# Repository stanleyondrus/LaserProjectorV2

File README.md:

## Introduction
LaserProjector V2 is a battery-powered, ESP32-based laser XY scanner using stepper motors to deflect the beam. It has auto-homing functionality, and can be controlled wirelessly (Wi-Fi & Bluetooth).

## Features
- Hybrid Wi-Fi operation mode (STA & AP)
- Webserver GUI with custom WebSocket protocol
- Concurrent multi-user control
- Automatic/Manual/External scanning mode
- Parallel auto-homing
- Battery-powered

## Links
- [Documentation [stanleyprojects.com]](https://stanleyprojects.com/projects/laserprojector-v2/)
- [Article [hackaday.com]](https://hackaday.com/2022/11/02/laser-project-relies-on-steppers-rather-than-galvanometers/)
- [Video [youtube.com]](https://youtu.be/w1O48Ysdiiw)
- [Project [hackaday.io]](https://hackaday.io/project/188046-laserprojector-v2)
- [Project [hackster.io]](https://www.hackster.io/stanleyprojects/laserprojector-v2-fa77cf)

## Design

## How to build your own release
### Prerequisites
- Visual Studio Code with PlatformIO extension
- 3.3V USB to Serial (e.g. FT232RL)
### Building
1. Open __*firmware/src*__ folder in VSCode
2. In __*firmware/src/src/main.cpp*__ you can sustomize SSID and PASSWORD for Wi-Fi STA mode:
```cpp
const char* ssid = "<your_ssid>";
const char* password = "<your_pass>";
```
3. In __*firmware/src/platformio.ini*__ set the correct *_upload_port_*, or remove to auto-detect.

4. Build and upload the filesystem
    - PlatformIO > esp32serial > Platform > Build Filesystem Image
    - PlatformIO > esp32serial > Platform > Upload Filesystem Image

5. Build and upload the firmware
    - PlatformIO > esp32serial > General > Upload

## Pre-built binaries
The binary is fully contained (bootloader, firmware, and filesystem), so it can be flashed to address 0x0.

The easiest way is to use this web tool: https://stanleyprojects.com/projects/laserprojector-v2/install/index.html

After the firmware is loaded, any subsequent updates can be done OTA in browser by visiting _http://\<esp32-ip-address\>/update_

|Version|Firmware|
|-|-|
|0.1|[LaserProjectorV2_firmware_v0.1.bin](https://github.com/stanleyondrus/LaserProjectorV2/releases/download/v0.1/LaserProjectorV2_v0.1.bin)|

## Credits
- [A Beginner's Guide to the ESP8266](https://tttapa.github.io/ESP8266/Chap01%20-%20ESP8266.html)
- [ElegantOTA](https://github.com/ayushsharma82/ElegantOTA)
- [StepperDriver](https://github.com/laurb9/StepperDriver)

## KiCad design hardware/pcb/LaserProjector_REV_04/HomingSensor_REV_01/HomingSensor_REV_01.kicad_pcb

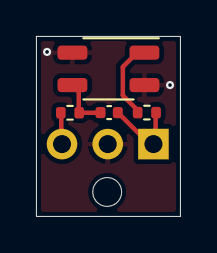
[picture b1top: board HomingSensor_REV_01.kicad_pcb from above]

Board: 2 copper layers, 8.0 x 10.0 mm, 5 parts (1 on the bottom side), 5 nets.

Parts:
C1: 10nF; C_0402_1005Metric
J2: Connector; PinSocket_1x03_P2.54mm_Vertical
R1: 100R; R_0402_1005Metric
R2: 220R; R_0402_1005Metric
U1: QRE1113; OnSemi_CASE100CY

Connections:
+3V3: C1.1, J2.1, R1.2
GND: J2.2, U1.2, U1.4
unnamed: C1.2, R2.2, U1.3
unnamed: R1.1, U1.1
OUT: J2.3, R2.1

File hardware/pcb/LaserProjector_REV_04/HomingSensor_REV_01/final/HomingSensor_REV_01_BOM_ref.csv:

"Ref","Value","MPN","Manufacturer","Package","Datasheet"
"C1","10nF","CL05B103KB5NNNC","Samsung Electro-Mechanics","0402","https://datasheet.lcsc.com/szlcsc/1810191223_Samsung-Electro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"
"R1","100R","AC0402FR-07100RL","Yageo","0402","https://eu.mouser.com/datasheet/2/447/PYu-AC_51_RoHS_L_7-171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"
"R2","220R","0402WGF2200TCE","UNI-ROYAL","0402","https://datasheet.lcsc.com/szlcsc/1811011214_UNI-ROYAL-Uniro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"
"U1","QRE1113","","","","http://www.onsemi.com/pub/Collateral/QRE1113-D.PDF"

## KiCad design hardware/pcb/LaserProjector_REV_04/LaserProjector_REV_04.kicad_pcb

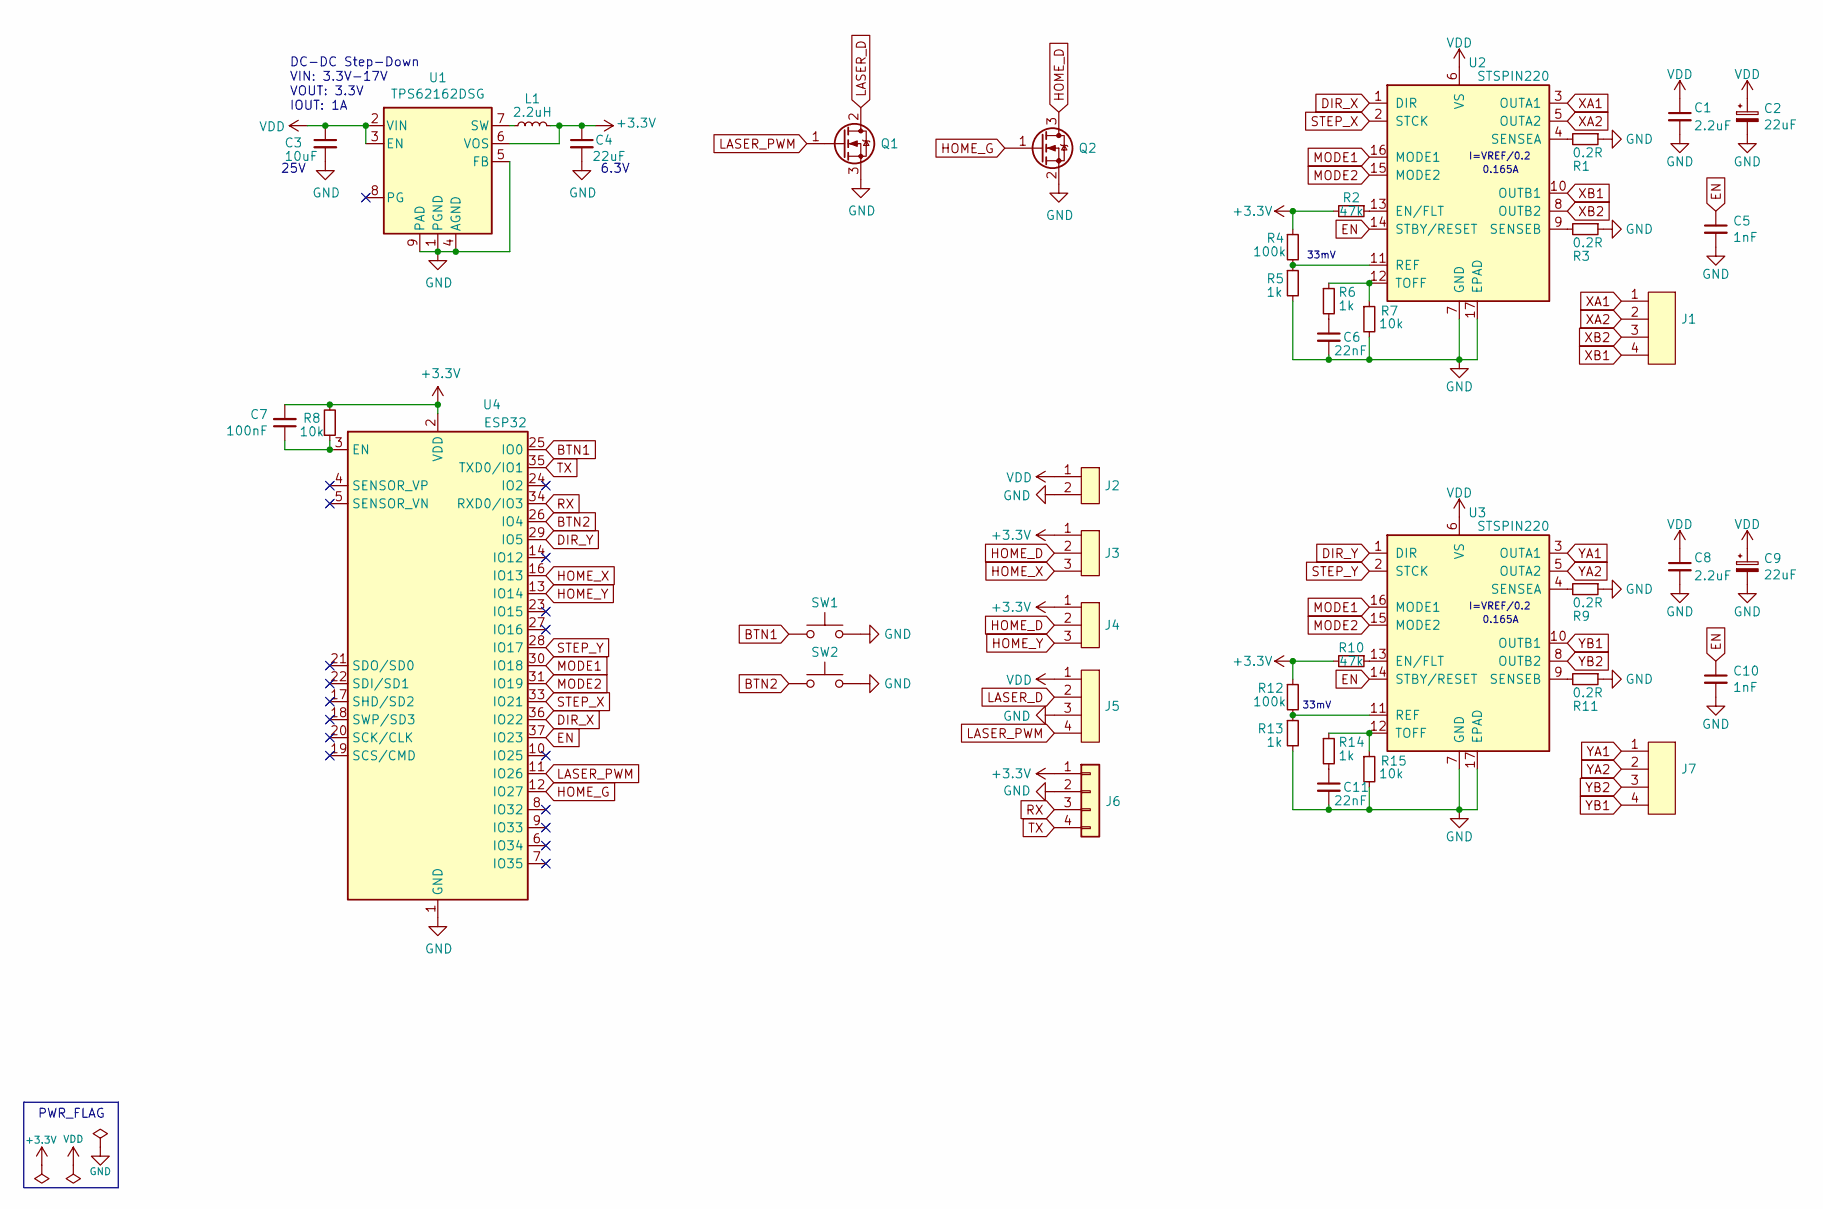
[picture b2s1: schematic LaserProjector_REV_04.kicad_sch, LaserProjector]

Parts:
C1, C8: 2.2uF; C_0603_1608Metric; MPN GRM188R61H225KE11D
C2, C9: 22uF; CP_Elec_6.3x5.8; MPN EEEHBH220UAP
C3: 10uF; C_0805_2012Metric; MPN CL21A106KAYNNNE
C4: 22uF; C_0805_2012Metric; MPN C2012X5R0J226MT000N
C5, C10: 1nF; C_0402_1005Metric; MPN GCM155R71H102KA37D
C6, C11: 22nF; C_0402_1005Metric; MPN GRM155R71E223JA61D
C7: 100nF; C_0402_1005Metric; MPN CC0402KRX7R7BB104
J1, J7: J_Molex-PicoBlade-4P-P1.25mm; Molex_PicoBlade_53047-0410_1x04_P1.25mm_Vertical; MPN 0530470410
J2: JST-XH-B2B; JST_XH_B2B-XH-A_1x02_P2.50mm_Vertical; MPN B2B-XH-A(LF)(SN)
J3, J4: J_Molex-PicoBlade-3P-P1.25mm; Molex_PicoBlade_53047-0310_1x03_P1.25mm_Vertical; MPN 0530470310
J5: JST-XH-B4B; JST_XH_B4B-XH-A_1x04_P2.50mm_Vertical; MPN B4B-XH-A(LF)(SN)
J6: Conn_01x04; PinHeader_1x04_P2.54mm_Vertical
L1: 2.2uH; VLCF4020; MPN VLCF4020T-2R2N1R7
Q1: NCE2060K; TO-252-2; MPN NCE2060K
Q2: NMOS; SOT-23; MPN NTR4501NT1G
R1, R3, R9, R11: 0.2R; R_2512_6332Metric; MPN WW25WR200FTL
R2, R10: 47k; R_0402_1005Metric; MPN RC0402FR-0747KL
R4, R12: 100k; R_0402_1005Metric; MPN RT0402BRE07100KL
R5, R6, R13, R14: 1k; R_0402_1005Metric; MPN 0402WGF1001TCE
R7, R8, R15: 10k; R_0402_1005Metric; MPN RT0402BRD0710KL
SW1, SW2: EVPAA602W; SW_EVPAA; MPN EVPAA602W
U1: TPS62162DSG; WSON-8-1EP_2x2mm_P0.5mm_EP0.9x1.6mm_ThermalVias; MPN TPS62162DSG
U2, U3: STSPIN220; MPN STSPIN220
U4: ESP32; ESP32-WROOM-32

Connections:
+3V3: C4.1, C7.2, J3.1, J4.1, J6.1, L1.2, R2.2, R4.1, R8.2, R10.2, R12.1, U1.6 (VOS), U4.2 (VDD)
BTN1: SW1.1, SW1.3, U4.25 (IO0); also elsewhere on the board
BTN2: SW2.1, SW2.3, U4.26 (IO4); also elsewhere on the board
DIR_X: U2.1 (DIR), U4.36 (IO22)
DIR_Y: U3.1 (DIR), U4.29 (IO5)
EN: C5.1, C10.1, U2.14 (STBY/RESET), U3.14 (STBY/RESET), U4.37 (IO23)
GND: C1.2, C2.2, C3.2, C4.2, C5.2, C6.2, C8.2, C9.2, C10.2, C11.2, J2.2, J5.3, J6.2, Q1.3 (S), Q2.2 (S), R1.1, R3.1, R5.2, R7.2, R9.1, R11.1, R13.2, R15.2, SW1.2, SW1.4, SW2.2, SW2.4, U1.1 (PGND), U1.4 (AGND), U1.5 (FB), U1.8 (PG), U1.9 (PAD), U2.7 (GND), U2.17 (EPAD), U3.7 (GND), U3.17 (EPAD), U4.1 (GND), U4.15 (GND), U4.38 (GND), U4.39 (GND); also elsewhere on the board
HOME_D: J3.2, J4.2, Q2.3 (D)
HOME_G: Q2.1 (G), U4.12 (IO27)
HOME_X: J3.3, U4.16 (IO13)
HOME_Y: J4.3, U4.13 (IO14)
LASER_D: J5.2, Q1.2 (D)
LASER_PWM: J5.4, Q1.1 (G), U4.11 (IO26)
MODE1: U2.16 (MODE1), U3.16 (MODE1), U4.30 (IO18)
MODE2: U2.15 (MODE2), U3.15 (MODE2), U4.31 (IO19)
unnamed: C6.1, R6.2
unnamed: C7.1, R8.1, U4.3 (EN)
unnamed: C11.1, R14.2
unnamed: L1.1, U1.7 (SW)
unnamed: R1.2, U2.4 (SENSEA)
unnamed: R2.1, U2.13 (EN/FLT)
unnamed: R3.2, U2.9 (SENSEB)
unnamed: R4.2, R5.1, U2.11 (REF)
unnamed: R6.1, R7.1, U2.12 (TOFF)
unnamed: R9.2, U3.4 (SENSEA)
unnamed: R10.1, U3.13 (EN/FLT)
unnamed: R11.2, U3.9 (SENSEB)
unnamed: R12.2, R13.1, U3.11 (REF)
unnamed: R14.1, R15.1, U3.12 (TOFF)
RX: J6.3, U4.34 (RXD0/IO3)
STEP_X: U2.2 (STCK), U4.33 (IO21)
STEP_Y: U3.2 (STCK), U4.28 (IO17)
TX: J6.4, U4.35 (TXD0/IO1)
VDD: C1.1, C2.1, C3.1, C8.1, C9.1, J2.1, J5.1, U1.2 (VIN), U1.3 (EN), U2.6 (VS), U3.6 (VS)
XA1: J1.1, U2.3 (OUTA1)
XA2: J1.2, U2.5 (OUTA2)
XB1: J1.4, U2.10 (OUTB1)
XB2: J1.3, U2.8 (OUTB2)
YA1: J7.1, U3.3 (OUTA1)
YA2: J7.2, U3.5 (OUTA2)
YB1: J7.4, U3.10 (OUTB1)
YB2: J7.3, U3.8 (OUTB2)

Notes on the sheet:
0.165A
PWR_FLAG
25V
6.3V
33mV
I=VREF/0.2
DC-DC Step-Down VIN: 3.3V-17V VOUT: 3.3V IOUT: 1A

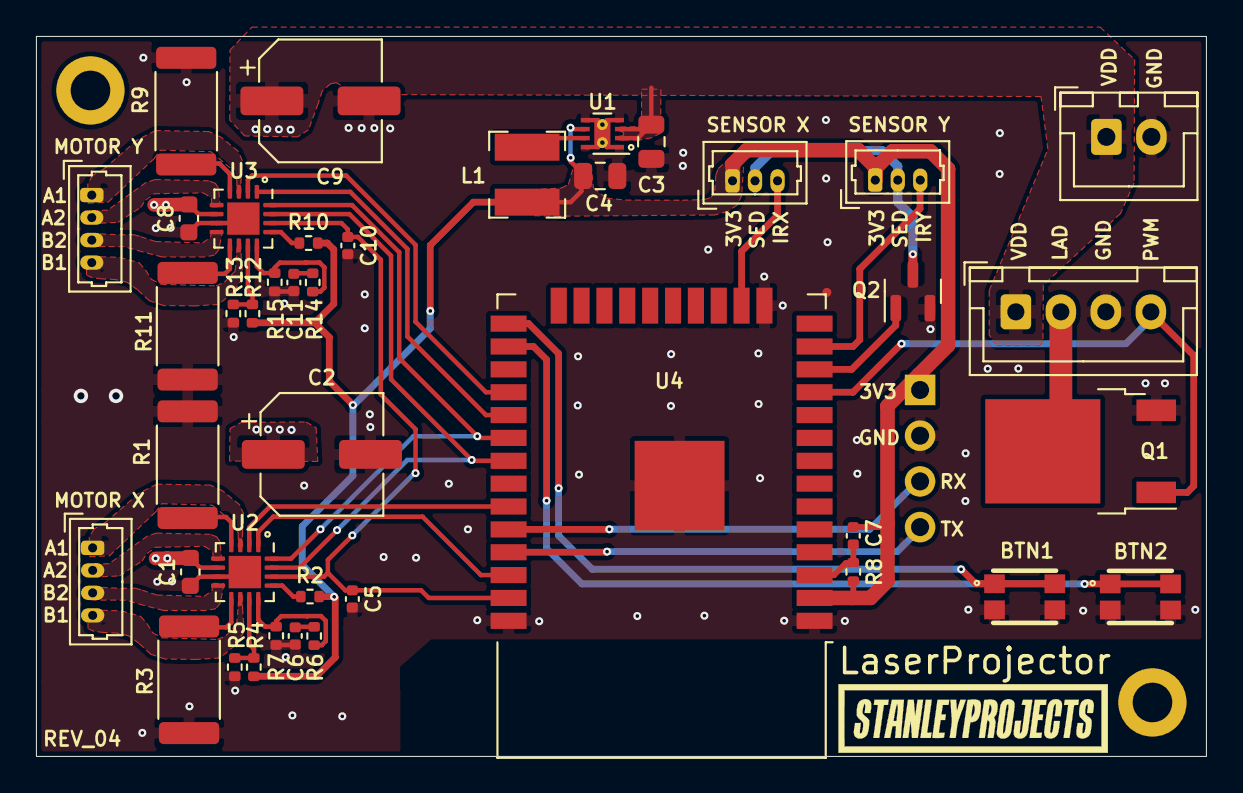
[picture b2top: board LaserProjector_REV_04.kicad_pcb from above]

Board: 2 copper layers, 65.0 x 40.0 mm, 42 parts (0 on the bottom side), 42 nets.

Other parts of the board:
BTN1, BTN2: EVPAA602W; SW_EVPAA

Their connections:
BTN1: BTN1.1, BTN1.3; also elsewhere on the board
BTN2: BTN2.1, BTN2.3; also elsewhere on the board
GND: BTN1.2, BTN1.4, BTN2.2, BTN2.4; also elsewhere on the board

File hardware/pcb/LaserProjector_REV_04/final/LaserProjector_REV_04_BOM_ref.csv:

"Ref","Value","MPN","Manufacturer","Package","Datasheet"
"C1","2.2uF","GRM188R61H225KE11D","Murata Electronics","0603","https://datasheet.lcsc.com/lcsc/1912111437_Murata-Electronic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"
"C2","22uF","EEEHBH220UAP","Panasonic","SMD (6.3x5.8mm)","https://datasheet.lcsc.com/lcsc/1912111437_PANASONIC-EEEHBH2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"
"C3","10uF","CL21A106KAYNNNE","Samsung Electro-Mechanics","0805","https://datasheet.lcsc.com/szlcsc/1811121310_Samsung-Electro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"
"C4","22uF","C2012X5R0J226MT000N","TDK","0805","https://datasheet.lcsc.com/szlcsc/1912111437_TDK-C2012X5R0J2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"
"C5","1nF","GCM155R71H102KA37D","Murata Electronics","0402","https://datasheet.lcsc.com/lcsc/1811081510_Murata-Electronic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"
"C6","22nF","GRM155R71E223JA61D","Murata Electronics","0402","https://datasheet.lcsc.com/lcsc/1912111437_Murata-Electronic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"
"C7","100nF","CC0402KRX7R7BB104","Yageo","0402","https://www.yageo.com/upload/media/product/productsearch/dat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"
"C8","2.2uF","GRM188R61H225KE11D","Murata Electronics","0603","https://datasheet.lcsc.com/lcsc/1912111437_Murata-Electronic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"
"C9","22uF","EEEHBH220UAP","Panasonic","SMD (6.3x5.8mm)","https://datasheet.lcsc.com/lcsc/1912111437_PANASONIC-EEEHBH2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"
"C10","1nF","GCM155R71H102KA37D","Murata Electronics","0402","https://datasheet.lcsc.com/lcsc/1811081510_Murata-Electronic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"
"C11","22nF","GRM155R71E223JA61D","Murata Electronics","0402","https://datasheet.lcsc.com/lcsc/1912111437_Murata-Electronic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"
"J1","J_Molex-PicoBlade-4P-P1.25mm","0530470410","Molex","Through Hole, P=1.25mm","https://www.molex.com/pdm_docs/sd/530470410_sd.pdf"
"J2","JST-XH-B2B","B2B-XH-A(LF)(SN)","JST Sales America","Through Hole, P=2.5mm","http://www.jst-mfg.com/product/pdf/eng/eXH.pdf"
"J3","J_Molex-PicoBlade-3P-P1.25mm","0530470310","Molex","Through Hole, P=1.25mm","https://www.molex.com/pdm_docs/sd/530470310_sd.pdf"
"J4","J_Molex-PicoBlade-3P-P1.25mm","0530470310","Molex","Through Hole, P=1.25mm","https://www.molex.com/pdm_docs/sd/530470310_sd.pdf"
"J5","JST-XH-B4B","B4B-XH-A(LF)(SN)","JST Sales America","Through Hole, P=2.5mm","https://datasheet.lcsc.com/szlcsc/1811151545_JST-Sales-Ameri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"
"J7","J_Molex-PicoBlade-4P-P1.25mm","0530470410","Molex","Through Hole, P=1.25mm","https://www.molex.com/pdm_docs/sd/530470410_sd.pdf"
"L1","2.2uH","VLCF4020T-2R2N1R7","TDK","4x4x2mm","https://datasheet.lcsc.com/szlcsc/1810211523_TDK-VLCF4020T-2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"
"Q1","NCE2060K","NCE2060K","Wuxi NCE Power Semiconductor","TO-252-2L","http://www.ncepower.com/Upload/MOSFET/NCE2060Kdatasheet-1511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"
"Q2","NMOS","NTR4501NT1G","ON Semicon","SOT-23","https://datasheet.lcsc.com/szlcsc/1810301530_ON-Semicon-NTR4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"
"R1","0.2R","WW25WR200FTL","Walsin Tech Corp","2512","https://datasheet.lcsc.com/lcsc/1912211104_Walsin-Tech-Corp-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"
"R2","47k","RC0402FR-0747KL","Yageo","0402","https://www.mouser.dk/datasheet/2/447/PYu_RC_Group_51_RoHS_L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"
"R3","0.2R","WW25WR200FTL","Walsin Tech Corp","2512","https://datasheet.lcsc.com/lcsc/1912211104_Walsin-Tech-Corp-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"
"R4","100k","RT0402BRE07100KL","YAGEO","0402","https://datasheet.lcsc.com/lcsc/1810241324_YAGEO-RT0402BRE07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"
"R5","1k","0402WGF1001TCE","Uniroyal Elec","0402","https://datasheet.lcsc.com/szlcsc/1811132311_Uniroyal-Elec-0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"
"R6","1k","0402WGF1001TCE","Uniroyal Elec","0402","https://datasheet.lcsc.com/szlcsc/1811132311_Uniroyal-Elec-0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"
"R7","10k","RT0402BRD0710KL","YAGEO","0402","https://datasheet.lcsc.com/szlcsc/1810241334_YAGEO-RT0402BRD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"
"R8","10k","RT0402BRD0710KL","YAGEO","0402","https://datasheet.lcsc.com/szlcsc/1810241334_YAGEO-RT0402BRD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"
"R9","0.2R","WW25WR200FTL","Walsin Tech Corp","2512","https://datasheet.lcsc.com/lcsc/1912211104_Walsin-Tech-Corp-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"
"R10","47k","RC0402FR-0747KL","Yageo","0402","https://www.mouser.dk/datasheet/2/447/PYu_RC_Group_51_RoHS_L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"
"R11","0.2R","WW25WR200FTL","Walsin Tech Corp","2512","https://datasheet.lcsc.com/lcsc/1912211104_Walsin-Tech-Corp-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"
"R12","100k","RT0402BRE07100KL","YAGEO","0402","https://datasheet.lcsc.com/lcsc/1810241324_YAGEO-RT0402BRE07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"
"R13","1k","0402WGF1001TCE","Uniroyal Elec","0402","https://datasheet.lcsc.com/szlcsc/1811132311_Uniroyal-Elec-0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"
"R14","1k","0402WGF1001TCE","Uniroyal Elec","0402","https://datasheet.lcsc.com/szlcsc/1811132311_Uniroyal-Elec-0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"
"R15","10k","RT0402BRD0710KL","YAGEO","0402","https://datasheet.lcsc.com/szlcsc/1810241334_YAGEO-RT0402BRD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"
"SW1","EVPAA602W","EVPAA602W","Panasonic","SMD","https://datasheet.lcsc.com/szlcsc/1809192044_PANASONIC-EVPAA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"
"SW2","EVPAA602W","EVPAA602W","Panasonic","SMD","https://datasheet.lcsc.com/szlcsc/1809192044_PANASONIC-EVPAA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"
"U1","TPS62162DSG","TPS62162DSG","Texas Instruments","WSON-8 (2x2mm)","https://datasheet.lcsc.com/lcsc/1806070425_Texas-Instruments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"
"U2","STSPIN220","STSPIN220","STMicroelectronics","VFQFPN 3x3x1.0","www.st.com/resource/en/datasheet/stspin220.pdf"
"U3","STSPIN220","STSPIN220","STMicroelectronics","VFQFPN 3x3x1.0","www.st.com/resource/en/datasheet/stspin220.pdf"
"U4","ESP32","","","","https://www.espressif.com/sites/default/files/documentation/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"

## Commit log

2016-03-31 [LaserControl.exe] fixed error when connecting to the wrong COM port [ArduinoLaserScanner.ino] ability to start/stop auto-mode remotely (star-pattern/STOP button while switch in auto-mode)
2017-08-28 LaserControl Source Code
2022-11-01 LaserProjector V2 - init
2022-11-02 Add hackaday.com link
2024-06-03 Update README.md
    update web installer update method
2024-06-03 replace two binaries with a single merged one
